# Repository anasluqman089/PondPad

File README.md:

# PondPad

Hello Everyone! PondPad is a custom arcade-style macropad built using a Seeed XIAO ESP32-C3. It uses 5 button, a TFT display and Bluetooth for quick shortcut, media, and text actions.

## Project contents

- Firmware: [Firmware/PondPadArcade.ino](Firmware/PondPadArcade.ino)
- Schematic and PCB: [PCB & Schematic/PondPad.kicad_sch](PCB%20%26%20Schematic/PondPad.kicad_sch) and [PCB & Schematic/PondPad.kicad_pcb](PCB%20%26%20Schematic/PondPad.kicad_pcb)
- Gerber output: [Production/Gerber](Production/Gerber)
- CAD files: [CAD](CAD)
- BOM: [BOM.csv](BOM.csv)

## Hardware

The current PCB is designed around:

- 1x Seeed XIAO ESP32-C3-SMD
- 5x Cherry MX-compatible 1.00u PCB switches
- 1x 240x320 ST7789-compatible TFT display
- 1x JST-PH 8-pin display interconnect
- 1x JST-PH 2-pin battery connector
- 4x M2 mounting holes

## BOM

| Name | Qty | Price | Buy Link |
| --- | ---: | --- | --- |
| Cherry MX switch | 5 | $8.75 | https://www.aliexpress.com/item/1005002162885278.html |
| XIAO ESP32-C3 | 1 | $12.00 | https://www.aliexpress.com/item/1005007469761633.html |
| JST PH 1x8 PCB mount | 1 | ~$0.20 | (Most only sells in pack more than 1) |
| JST PH 1x2 PCB mount | 1 | ~$0.20 | (Most only sells in pack more than 1) |
| M2 mounting screw | 4 | ~$0.50 | (Most only sells in pack more than 4) |
| 240x320 TFT display | 1 | $13.00 | https://www.aliexpress.com/item/1005008772378337.html] |
| PCB (With Stencil) | 1 | $7.80 | https://www.aliexpress.com/item/1005012672070003.html] |
| 3D Printing | 1 | ~$10.00 | - |

## Firmware

The firmware is written in Arduino C++.

### Required libraries

Install the following in the Arduino IDE or PlatformIO:

- Adafruit_GFX
- Adafruit_ST7789
- BleKeyboard
- Preferences support is built into the ESP32 core

### Pin map

The firmware expects the following GPIO assignments:

- Display backlight: GPIO 2
- Display reset: GPIO 3
- Display data/command: GPIO 4
- Display chip select: GPIO 5
- Key switches: GPIO 6, 7, 21, 9, 20
- SPI clock: GPIO 8
- SPI MOSI: GPIO 10

## Operation

The device starts in a menu screen and offers:

1. Macro pad mode
2. Fly Catch game
3. Whack-a-Frog game
4. Lily Dodge game
5. High score screen

The macro pad mode sends keyboard shortcuts and media commands over BLE to a paired host.

### Images

### PCB

### CAD

### Schematic

## License

This project is distributed under the repository license. See the [LICENSE](LICENSE) for details.

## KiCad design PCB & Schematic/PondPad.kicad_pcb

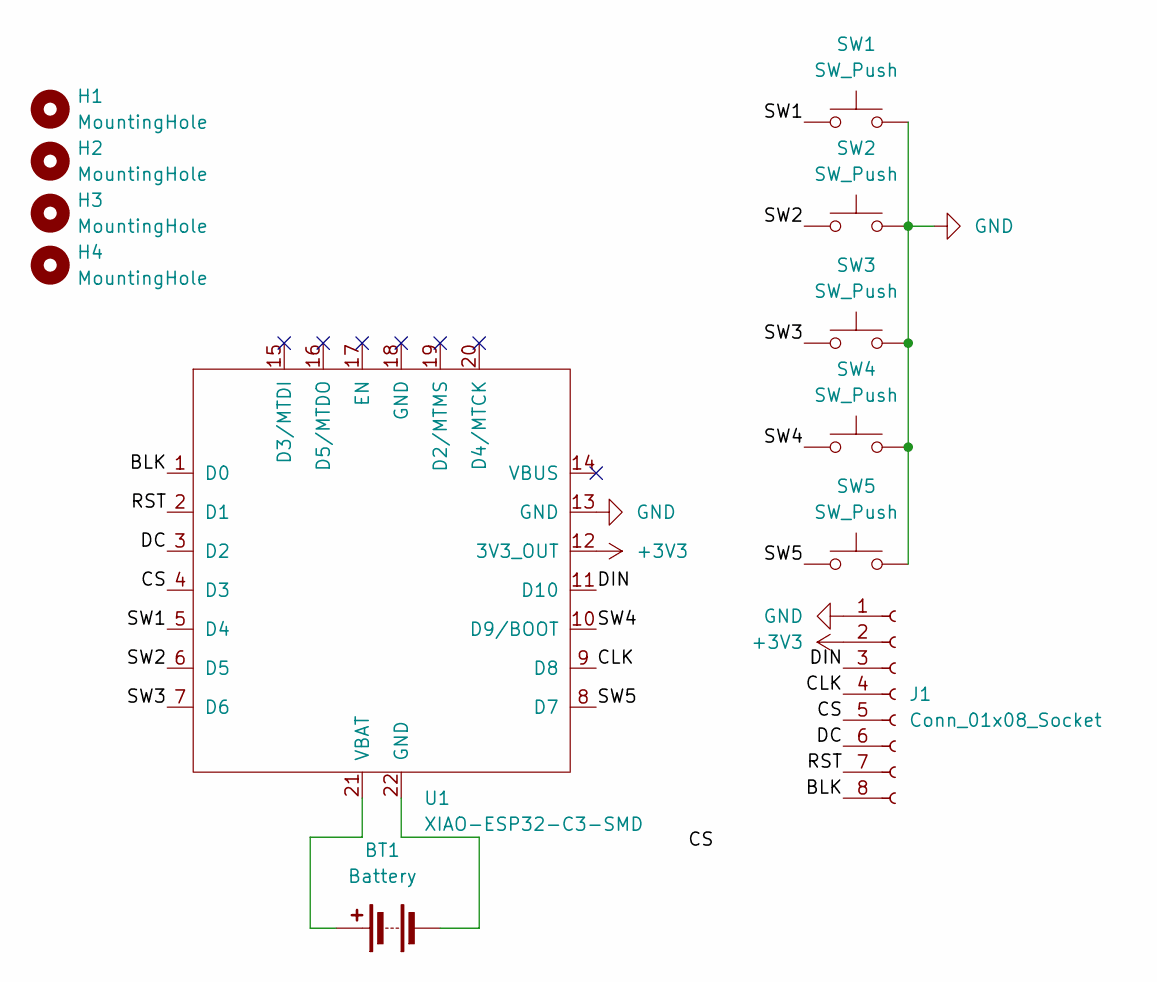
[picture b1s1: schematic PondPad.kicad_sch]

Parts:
BT1: Battery; JST_PH_S2B-PH-K_1x02_P2.00mm_Horizontal
H1, H2, H3, H4: MountingHole; MountingHole_2.2mm_M2
J1: Conn_01x08_Socket; JST_PH_S8B-PH-K_1x08_P2.00mm_Horizontal
SW1, SW2, SW3, SW4, SW5: SW_Push; SW_Cherry_MX_1.00u_PCB
U1: XIAO-ESP32-C3-SMD

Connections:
+3V3: J1.2, U1.12 (3V3_OUT)
/BLK: J1.8, U1.1 (D0)
/CLK: J1.4, U1.9 (D8)
/CS: J1.5, U1.4 (D3)
/DC: J1.6, U1.3 (D2)
/DIN: J1.3, U1.11 (D10)
/RST: J1.7, U1.2 (D1)
/SW1: SW1.1, U1.5 (D4)
/SW2: SW2.1, U1.6 (D5)
/SW3: SW3.1, U1.7 (D6)
/SW4: SW4.1, U1.10 (D9/BOOT)
/SW5: SW5.1, U1.8 (D7)
GND: J1.1, SW1.2, SW2.2, SW3.2, SW4.2, SW5.2, U1.13 (GND)
unnamed: BT1.1 (+), U1.21 (VBAT)
unnamed: BT1.2 (-), U1.22 (GND)

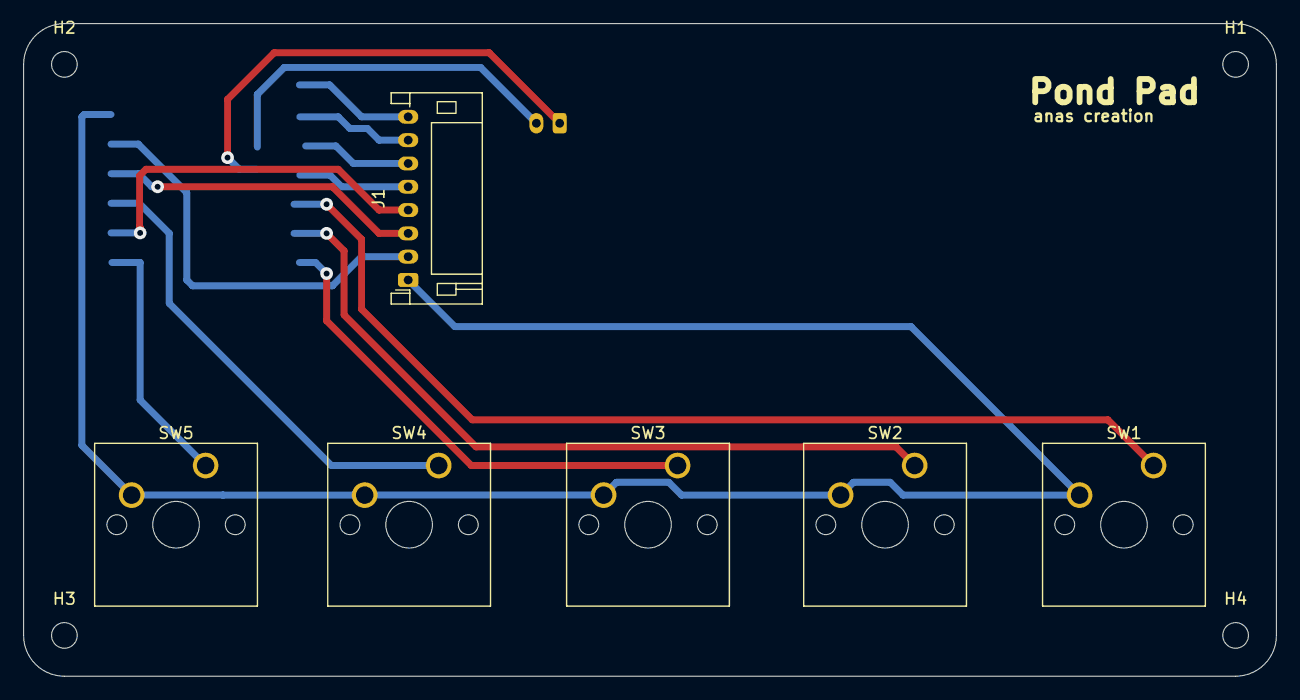
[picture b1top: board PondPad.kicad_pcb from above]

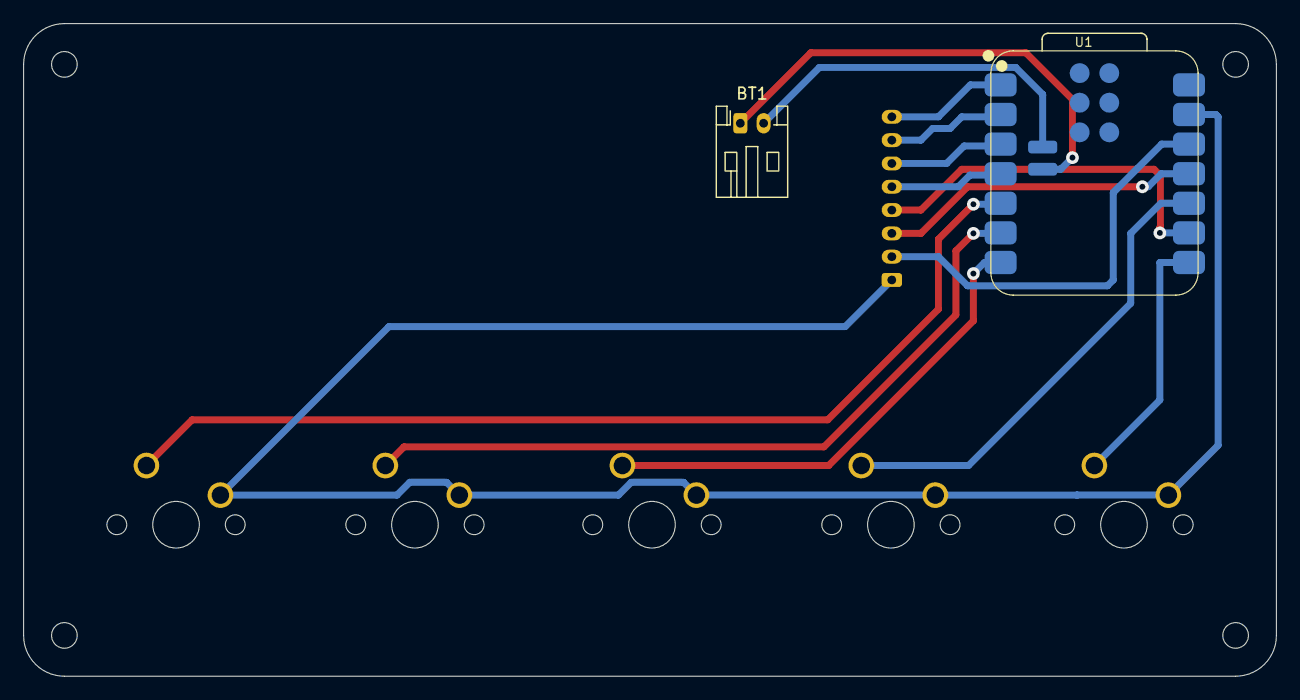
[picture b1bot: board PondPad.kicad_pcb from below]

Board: 2 copper layers, 107.5 x 56.0 mm, 12 parts (2 on the bottom side), 15 nets.
